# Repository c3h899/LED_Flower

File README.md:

# LED_Flower
Series-Parallel (8s3p) Arrangement of 1414/XHP35 LEDs (24 Resistors in Total)
- Approximately (2.5" x 2.51")
- 0805 Ballast Resistor Sites with Options for Solder Jumpers.
- Targeting (20 to 28) V DC Input Voltage.
- Arranged in a Octagonal Flower, each petal consists of 3 LEDs in Parallel.

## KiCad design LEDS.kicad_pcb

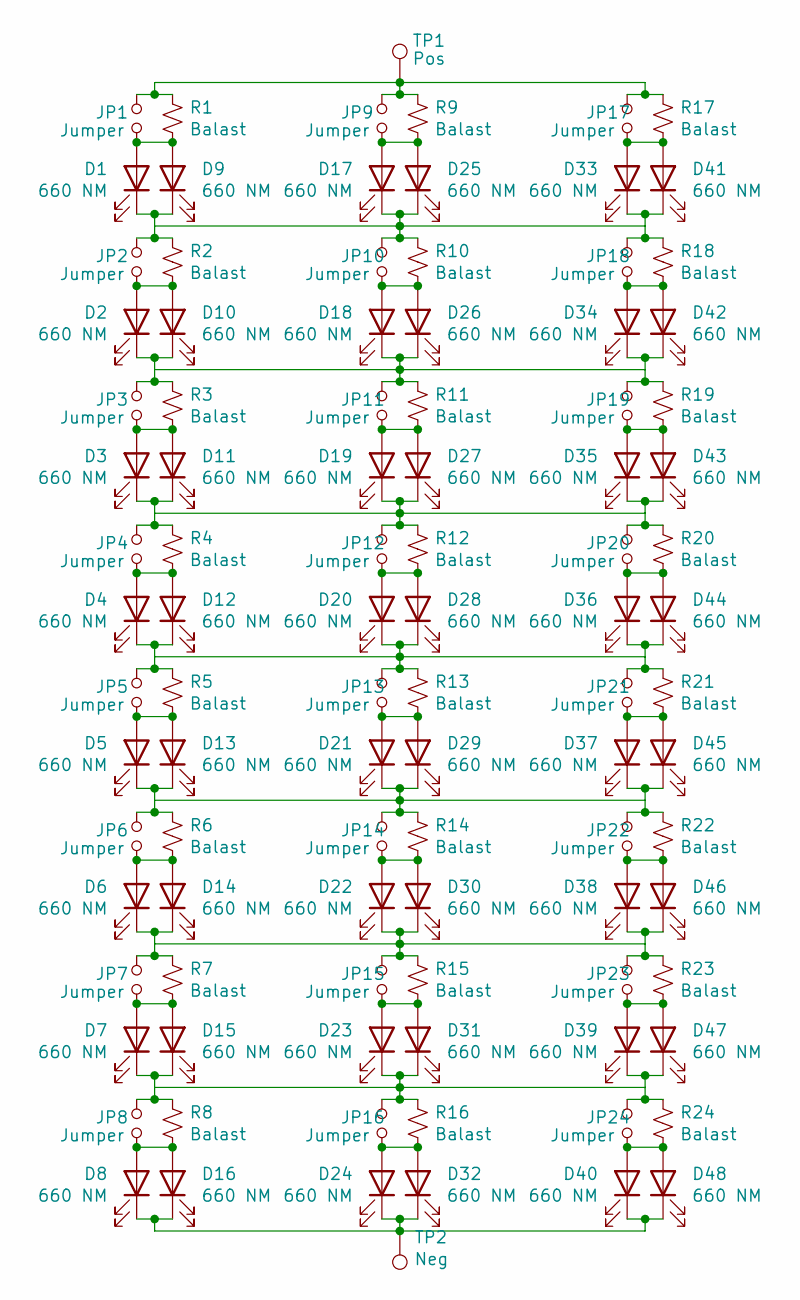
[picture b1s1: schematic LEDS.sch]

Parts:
D1, D2, D3, D4, D5, D6, D7, D8, D17, D18, D19, D20, D21, D22, D23, D24, D33, D34, D35, D36, D37, D38, D39, D40: 660 NM; LED_D3.0mm
D9, D10, D11, D12, D13, D14, D15, D16, D25, D26, D27, D28, D29, D30, D31, D32, D41, D42, D43, D44, D45, D46, D47, D48: 660 NM; LED_Cree-XHP35
JP1, JP2, JP3, JP4, JP5, JP6, JP7, JP8, JP9, JP10, JP11, JP12, JP13, JP14, JP15, JP16, JP17, JP18, JP19, JP20, JP21, JP22, JP23, JP24: Jumper; SolderJumper-2_P1.3mm_Open_Pad1.0x1.5mm
R1, R2, R3, R4, R5, R6, R7, R8, R9, R10, R11, R12, R13, R14, R15, R16, R17, R18, R19, R20, R21, R22, R23, R24: Balast; R_0805_2012Metric_Pad1.20x1.40mm_HandSolder
TP1: Pos; TestPoint_Pad_D4.0mm
TP2: Neg; TestPoint_Pad_D4.0mm

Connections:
unnamed: D1.1 (K), D9.1 (K), D17.1 (K), D25.1 (K), D33.1 (K), D41.1 (K), JP2.2, JP10.2, JP18.2, R2.1, R10.1, R18.1
unnamed: D1.2 (A), D9.2 (A), JP1.1, R1.2
unnamed: D2.1 (K), D10.1 (K), D18.1 (K), D26.1 (K), D34.1 (K), D42.1 (K), JP3.2, JP11.2, JP19.2, R3.1, R11.1, R19.1
unnamed: D2.2 (A), D10.2 (A), JP2.1, R2.2
unnamed: D3.1 (K), D11.1 (K), D19.1 (K), D27.1 (K), D35.1 (K), D43.1 (K), JP4.2, JP12.2, JP20.2, R4.1, R12.1, R20.1
unnamed: D3.2 (A), D11.2 (A), JP3.1, R3.2
unnamed: D4.1 (K), D12.1 (K), D20.1 (K), D28.1 (K), D36.1 (K), D44.1 (K), JP5.2, JP13.2, JP21.2, R5.1, R13.1, R21.1
unnamed: D4.2 (A), D12.2 (A), JP4.1, R4.2
unnamed: D5.1 (K), D13.1 (K), D21.1 (K), D29.1 (K), D37.1 (K), D45.1 (K), JP6.2, JP14.2, JP22.2, R6.1, R14.1, R22.1
unnamed: D5.2 (A), D13.2 (A), JP5.1, R5.2
unnamed: D6.1 (K), D14.1 (K), D22.1 (K), D30.1 (K), D38.1 (K), D46.1 (K), JP7.2, JP15.2, JP23.2, R7.1, R15.1, R23.1
unnamed: D6.2 (A), D14.2 (A), JP6.1, R6.2
unnamed: D7.1 (K), D15.1 (K), D23.1 (K), D31.1 (K), D39.1 (K), D47.1 (K), JP8.2, JP16.2, JP24.2, R8.1, R16.1, R24.1
unnamed: D7.2 (A), D15.2 (A), JP7.1, R7.2
unnamed: D8.1 (K), D9.3, D10.3, D11.3, D12.3, D13.3, D14.3, D15.3, D16.1 (K), D16.3, D24.1 (K), D25.3, D26.3, D27.3, D28.3, D29.3, D30.3, D31.3, D32.1 (K), D32.3, D40.1 (K), D41.3, D42.3, D43.3, D44.3, D45.3, D46.3, D47.3, D48.1 (K), D48.3, TP2.1
unnamed: D8.2 (A), D16.2 (A), JP8.1, R8.2
unnamed: D17.2 (A), D25.2 (A), JP9.1, R9.2
unnamed: D18.2 (A), D26.2 (A), JP10.1, R10.2
unnamed: D19.2 (A), D27.2 (A), JP11.1, R11.2
unnamed: D20.2 (A), D28.2 (A), JP12.1, R12.2
unnamed: D21.2 (A), D29.2 (A), JP13.1, R13.2
unnamed: D22.2 (A), D30.2 (A), JP14.1, R14.2
unnamed: D23.2 (A), D31.2 (A), JP15.1, R15.2
unnamed: D24.2 (A), D32.2 (A), JP16.1, R16.2
unnamed: D33.2 (A), D41.2 (A), JP17.1, R17.2
unnamed: D34.2 (A), D42.2 (A), JP18.1, R18.2
unnamed: D35.2 (A), D43.2 (A), JP19.1, R19.2
unnamed: D36.2 (A), D44.2 (A), JP20.1, R20.2
unnamed: D37.2 (A), D45.2 (A), JP21.1, R21.2
unnamed: D38.2 (A), D46.2 (A), JP22.1, R22.2
unnamed: D39.2 (A), D47.2 (A), JP23.1, R23.2
unnamed: D40.2 (A), D48.2 (A), JP24.1, R24.2
unnamed 32: JP1.2, JP9.2, JP17.2, R1.1, R9.1, R17.1, TP1.1; also elsewhere on the board

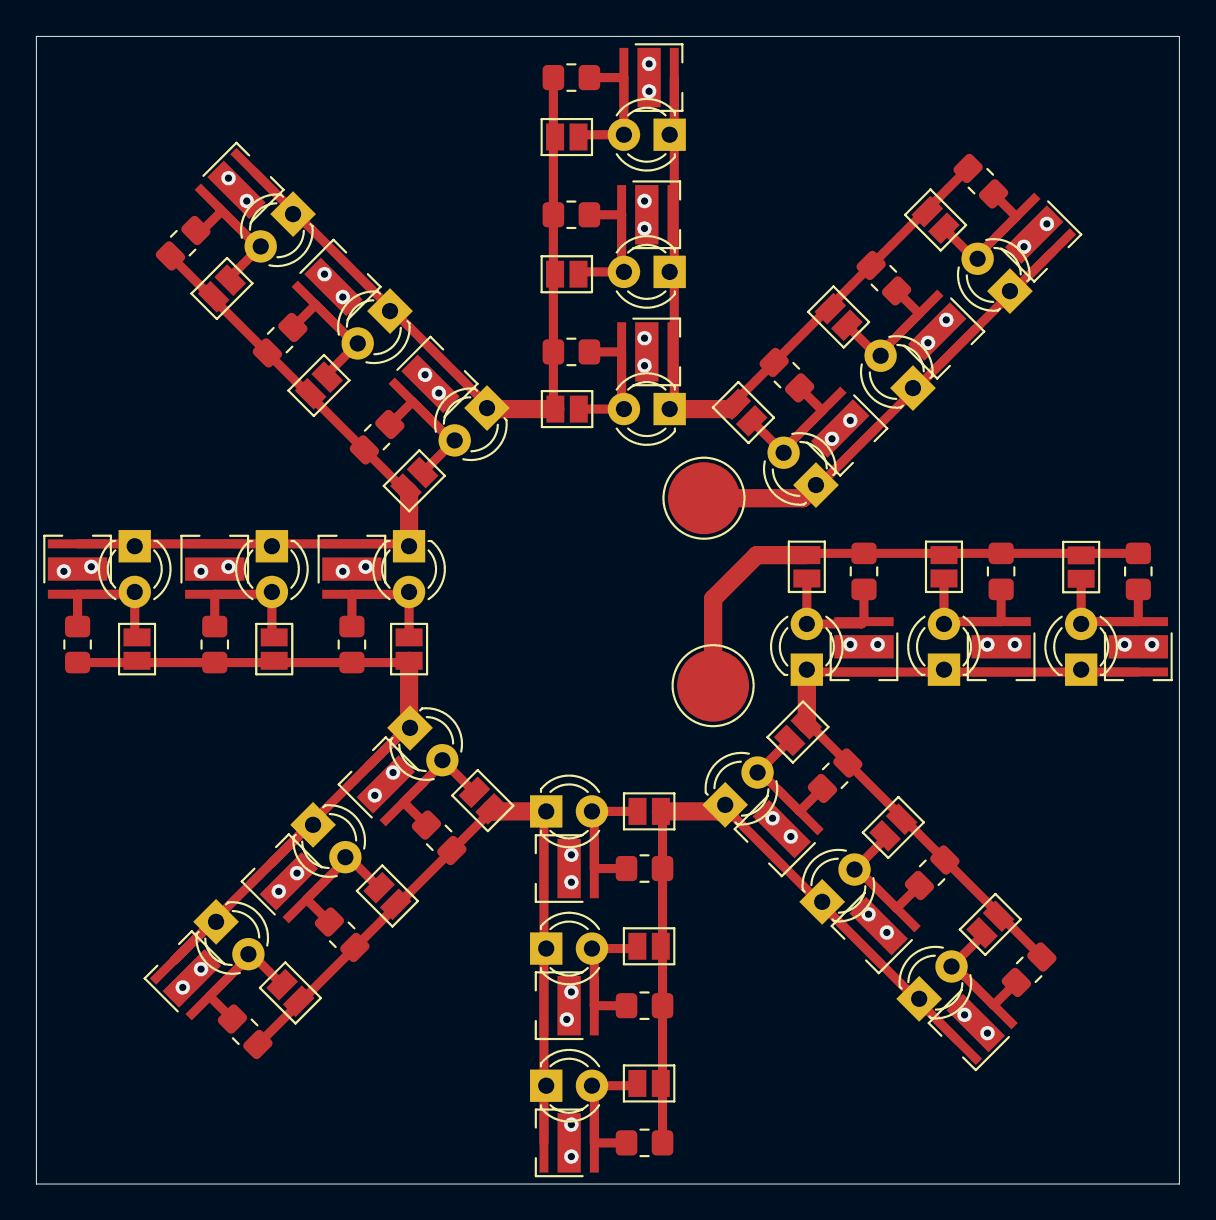
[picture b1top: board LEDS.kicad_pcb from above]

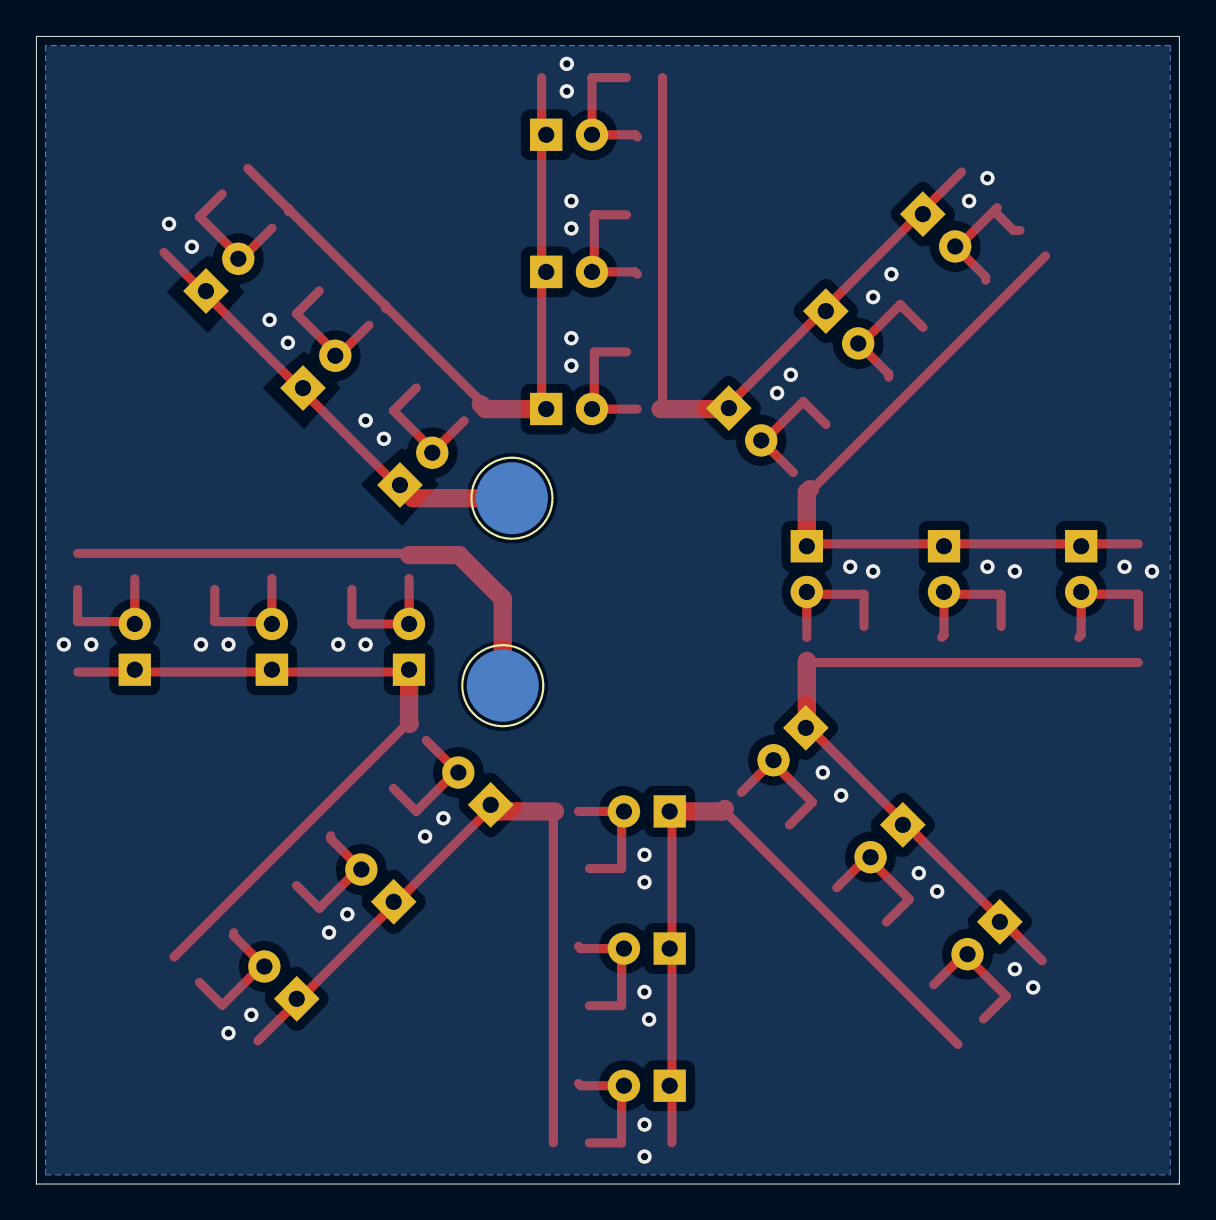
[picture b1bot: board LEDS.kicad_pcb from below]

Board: 2 copper layers, 63.5 x 63.8 mm, 100 parts (2 on the bottom side), 33 nets.

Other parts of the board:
TP1#2, TP1#3: Pos; TestPoint_Pad_D4.0mm

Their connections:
unnamed 32: TP1#3.1; also elsewhere on the board

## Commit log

2025-04-11 Initial Upload
